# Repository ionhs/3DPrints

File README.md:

# 3DPrints

Lista de componentes diseñados en 3D que he ido recopilando de diferentes sitios o creándolos:

| Nombre                                                                 | Master                                                                                  | Modif | Archivo     | Fecha     |
| ------------------------------------------------------------------------ | :---------------------------------------------------------------------------------------- | ------- | ------------- | ----------- |
| [PCBbutton](https://github.com/ionhsFP/3DPrints/tree/master/PCBbutton) | [Obijuan](https://github.com/PCBPrints/Alhambra-button)                                 | No    | STL         | 9-10-2018 |
| [PCBLed](https://github.com/ionhsFP/3DPrints/tree/master/PCBLed)       | [javacasm](https://github.com/PCBPrints/PCbPrints/tree/master/PCBPrint_button_with_lid) | Si    | Freecad+STL | 9-10-2018 |
| [Pisua](https://github.com/ionhsFP/3DPrints/tree/master/Pisua)         | i.hernandez                                                                             | No    | Freecad+STL | 9-10-2018 |
| [Filtro](https://github.com/ionhsFP/3DPrints/tree/master/Filtro)        | i.hernandez                                                                             | No    | Freecad+STL | 9-7-2024  |

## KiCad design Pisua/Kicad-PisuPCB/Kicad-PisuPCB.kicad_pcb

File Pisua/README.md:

# Báscula de control de peso

El objetivo es documentar la realización una báscula de control de peso didáctica para identificar mediante 4 sensores, diferentes tipos de peso. De esta manera se puede trabajar las competencias de "Electrónica microprogramable" del ciclo de grado superior de "Mantenimiento Electrónico" relacionados con los conocimientos de electrónica combinacional (Puertas lógicas, multiplexores, decodificadores...). Tanto con chips combinacionales así como con FPGAs.

La báscula está compuesta de piezas impresas en 3D que está disponibles en este repositorio, [tanto en STL como en Freecad](./Piezas) para su impresión y modificación. Además es necesario 4 finales de carrera (aunque se podría con menos).

Por otra parte se ha diseñado una pequeña PCB en Kicad para facilitar el cableado del circuito.

## Piezas 3D

|  Nº  |     Archivo     |                         Descripción                          |                 Imagen                 |
| :--: | :-------------: | :----------------------------------------------------------: | :------------------------------------: |
|  1   |      Base       |      Base de báscula para apoyar el peso en la báscula       |                   |
|  1   |     Báscula     | Estructura de la báscula donde se sustentan todas las piezas |           |
|  1   | Báscula Lateral |  Pieza lateral de la báscula al que se apoyan los sensores   |  |
|  4   | Báscula sensor  | Pieza donde se ajusta los sensores y se calibran los sensores |    |

## Componentes Mecánicos

|  Nº  |     Nombre      |                         Descripción                          |                            Imagen                            |
| :--: | :-------------: | :----------------------------------------------------------: | :----------------------------------------------------------: |
|  10  | Tornillos M3x6  |           Tornillos métricos philips de acero M3x6           |                                |
|  6   | Tornillos M3x10 |          Tornillos métricos philips de acero M3x10           |                                |
|  1   |     Esponja     |              Esponja de dimensiones 11x9,5x2,5               |                                      |
|  4   |    Sensores     | Final de carrera de movimiento ENDSTOP para ramps 1,4 impresora 3D CR-10 CR-10S CR-S4 CR-S |                                |
|  4   |      Cable      | 3 cables multihilos con conectores para los sensores finales de carrera |                                        |
|  1   |       PCB       | PCB del circuito diseñado en [Kicad](./Kicad-PisuPCB), con su [archivo CAM](./Kicad-PisuPCB/PCB_pisua_LPKF.cam) (CircuitCAM) y su [archivo BroadMaster](./Kicad-PisuPCB/PCB_pisua_LPKF.LMD) para mecanizar en la LPKF |  |

## Montaje de la báscula

1. Sobre la pieza impresa en 3D "báscula lateral", atornillamos la PCB con 2 tornillos M3x6
2. Sobre las piezas impresas en 3D "báscula sensor", atornillamos los sensores con 2 tornillos M3x6 por sensor a diferentes alturas cada sensor.
3. Colocamos sobre la pieza "báscula lateral", las piezas impresas en 3D "báscula sensor" mediante tornillos M3x10.
4. Juntamos la "báscula lateral" sobre la pieza impresa en 3D "báscula".
5. Solo queda colocar la esponja y sobre ella la pieza impresa en 3D "base".
6. Tras finalizar el montaje solo queda ajustar cada pieza "báscula sensor" acercándola a la base de manera que permita ser pulsado el sensor por la base.

Fotos del proceso de montaje de la báscula:

|                  1                   |                  2                   |                  3                   |
| :----------------------------------: | :----------------------------------: | :----------------------------------: |
|  |  |  |
|                **4**                 |                **5**                 |                **6**                 |
|  |  |  |

* El cableado de los sensores a la PCB, se ha recortado a una medida ajustada y en un extremo se han puesto conectores futaba o JR.
* 

## Funcionamiento eléctrico

Las señales de conexión de los 4 sensores, cuando están sin pulsar los sensores están en alta impedancia (circuitos abiertos ). Al pulsar los sensores la señal de salida del sensor estará conectada a masa. Por este motivo para poder usarse estos sensores se deberá una resistencias en pull-up de 10K ohm por sensor.

No hay que olvidarse de alimentar los 4 sensores, conectandolos a una fuente de alimentación de 5V y GND sus respectivos pines.

Otra posibilidad en vez de montar los pull-up con resistencias fuera, es hacerlo mediante la activación de resistencias internas. En este caso se pueden ver los montajes con resistencias externas y con resistencias internas usando una placa [FPGA libre Alhambra II](https://groups.google.com/forum/#!forum/fpga-wars-explorando-el-lado-libre).

|  |      |  |
| ------------------------------------- | ---------------------------- | ------------------------------------- |
| Circuito con Pull-up ext.             | Programación de Pull-up int. | Circuito con Pull-up int.             |

## Mejoras futuras pendientes

Sustituir la espoja por algún sistema amortiguado que se adecue mejor a un funcionamiento real.

Mejorar el sistema mecánico para hacerlo con un diseño más atractivo y más robusto.

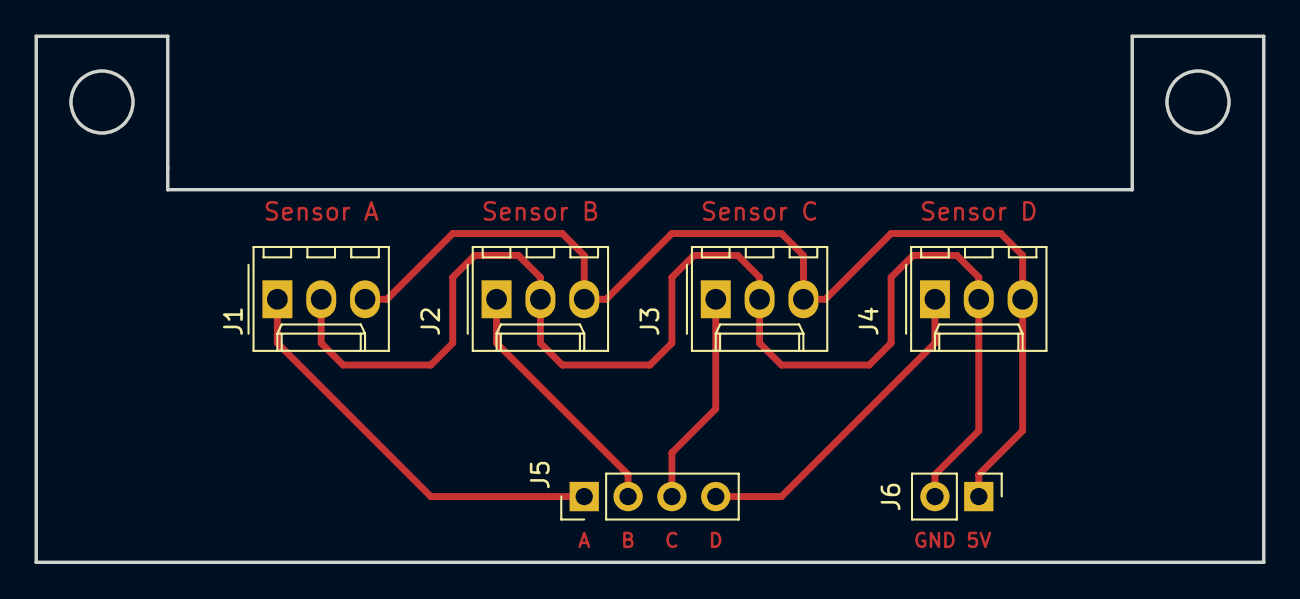
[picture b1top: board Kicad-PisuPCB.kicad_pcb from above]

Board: 2 copper layers, 71.1 x 30.5 mm, 6 parts (0 on the bottom side), 6 nets.

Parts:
J1: Sensor A; Molex_KK-254_AE-6410-03A_1x03_P2.54mm_Vertical
J2: Sensor B; Molex_KK-254_AE-6410-03A_1x03_P2.54mm_Vertical
J3: Sensor C; Molex_KK-254_AE-6410-03A_1x03_P2.54mm_Vertical
J4: Sensor D; Molex_KK-254_AE-6410-03A_1x03_P2.54mm_Vertical
J5: Sensores; PinHeader_1x04_P2.54mm_Vertical
J6: Power; PinHeader_1x02_P2.54mm_Vertical

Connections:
+5V: J1.3, J2.3, J3.3, J4.3, J6.1
GND: J1.2, J2.2, J3.2, J4.2, J6.2
unnamed: J1.1, J5.1
unnamed: J2.1, J5.2
unnamed: J3.1, J5.3
unnamed: J4.1, J5.4

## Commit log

2018-10-09 Actualización de PCBprint y Pisua
2018-10-09 actualizacion
2018-10-09 actualizar
2018-10-15 PCB-LED creado desde cero
2018-10-23 Actualización de bascula hasta fase de montaje alpha
2018-11-06 Versión 1.0V operativa de las piezas STL
2018-12-11 Actualización de Bloques para canicas
2019-02-09 Añadida base a la báscula
2019-03-13 Añadir Circuito Kicad y actualizar pieza de la báscula
2019-09-10 Creación de bascula
2019-09-10 bugs
2019-09-10 Actualizado link de las fotos
2019-09-10 actualización bug links de las fotos
2019-09-10 actualizacion de video
2019-09-13 Añadido fotos del circuito montado
2019-10-07 Circuitmaker y BroadMaster
2024-07-09 Añadido Filtro a la colección de piezas 3D
2024-07-09 actualizacion de link
2024-07-09 cambio del grosor de la pieza externa
